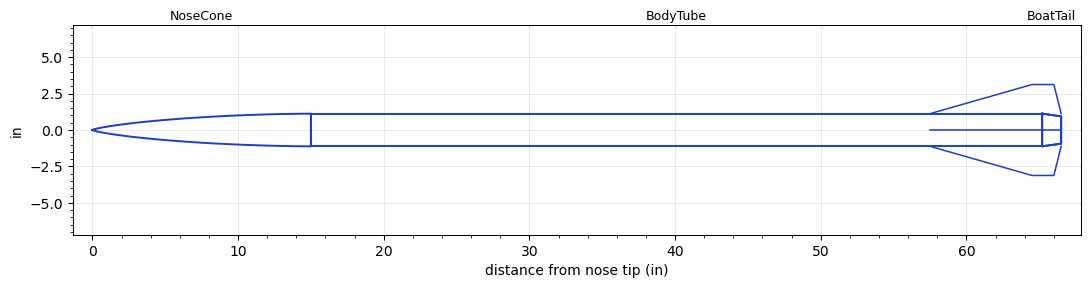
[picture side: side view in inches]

<RASAeroDocument>
 <FileVersion>2</FileVersion>
 <RocketDesign>
  <NoseCone>
   <Length>15</Length>
   <Diameter>2.242</Diameter>
   <Shape>LV-Haack</Shape>
   <Location>0</Location>
  </NoseCone>
  <BodyTube>
   <Length>50.2</Length>
   <Diameter>2.242</Diameter>
   <Location>15</Location>
   <BoattailLength>1.305</BoattailLength>
   <BoattailRearDiameter>1.875</BoattailRearDiameter>
   <Overhang>1.305</Overhang>
   <Fin>
    <Count>4</Count>
    <Chord>9</Chord>
    <Span>2</Span>
    <SweepDistance>7</SweepDistance>
    <TipChord>1.5</TipChord>
    <Thickness>0.125</Thickness>
    <LERadius>0.05</LERadius>
    <Location>7.695</Location>
    <AirfoilSection>Hexagonal</AirfoilSection>
    <FX1>0.3</FX1>
    <FX3>0.3</FX3>
   </Fin>
  </BodyTube>
  <BoatTail>
   <Length>1.305</Length>
   <Diameter>2.242</Diameter>
   <RearDiameter>1.875</RearDiameter>
   <Location>65.2</Location>
  </BoatTail>
  <Surface>Camouflage Paint</Surface>
  <ModifiedBarrowman>True</ModifiedBarrowman>
  <Turbulence>True</Turbulence>
  <UseBooster1>False</UseBooster1>
  <UseBooster2>False</UseBooster2>
 </RocketDesign>
 <LaunchSite>
  <Altitude>4000</Altitude>
  <Pressure>0</Pressure>
  <RodAngle>2</RodAngle>
  <RodLength>10</RodLength>
  <Temperature>85</Temperature>
  <WindSpeed>10</WindSpeed>
 </LaunchSite>
 <Recovery>
  <Altitude1>1000</Altitude1>
  <Altitude2>1000</Altitude2>
  <DeviceType1>None</DeviceType1>
  <DeviceType2>None</DeviceType2>
  <Event1>False</Event1>
  <Event2>False</Event2>
  <Size1>1</Size1>
  <Size2>1</Size2>
  <EventType1>None</EventType1>
  <EventType2>None</EventType2>
  <CD1>1.33</CD1>
  <CD2>1.33</CD2>
 </Recovery>
 <SimulationList>
  <Simulation>
   <SustainerEngine>M1378LR  (Loki)</SustainerEngine>
   <SustainerLaunchWt>12.6</SustainerLaunchWt>
   <SustainerNozzleDiameter>1.8</SustainerNozzleDiameter>
   <SustainerCG>41.1</SustainerCG>
   <SustainerIgnitionDelay>0</SustainerIgnitionDelay>
   <Booster1SeparationDelay>0</Booster1SeparationDelay>
   <Booster1IgnitionDelay>0</Booster1IgnitionDelay>
   <IncludeBooster1>False</IncludeBooster1>
   <Booster2Delay>0</Booster2Delay>
   <IncludeBooster2>False</IncludeBooster2>
   <TimetoApogee>49.18775</TimetoApogee>
   <MaxAltitude>53332.1</MaxAltitude>
   <MaxVelocity>3401.132</MaxVelocity>
  </Simulation>
 </SimulationList>
</RASAeroDocument>
